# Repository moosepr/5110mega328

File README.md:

# 5110mega328
A tiny board with 5110 screen, atmega 328 and accelerometer

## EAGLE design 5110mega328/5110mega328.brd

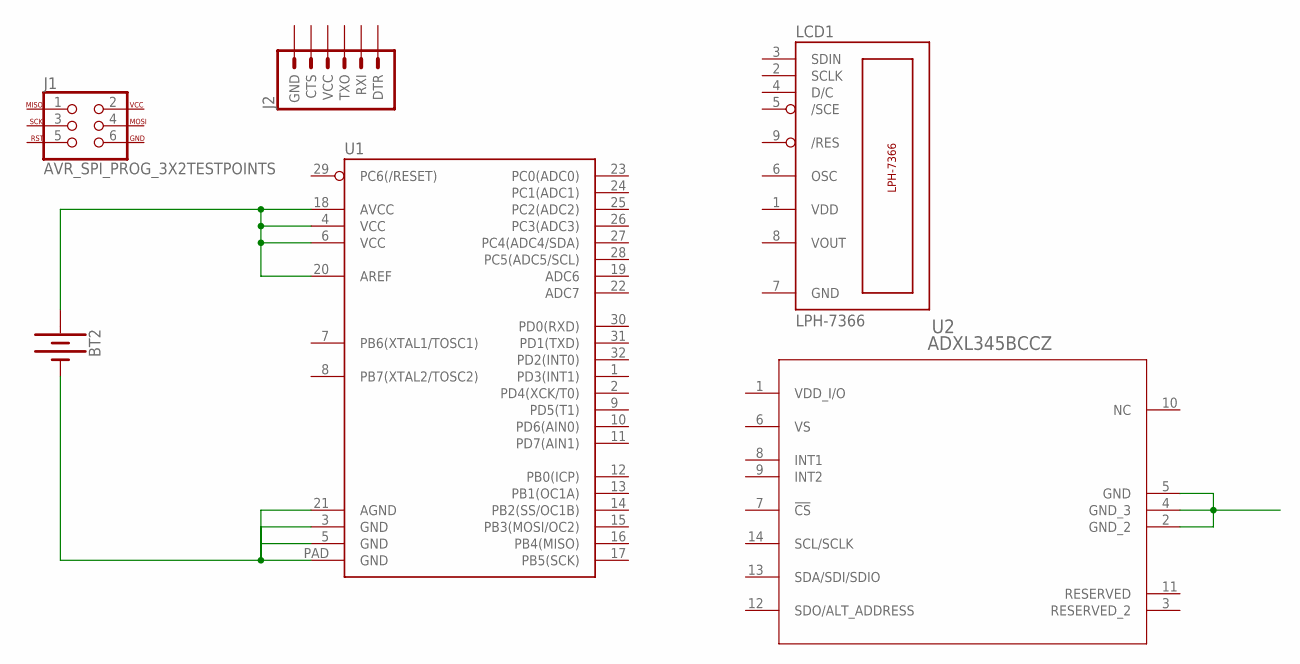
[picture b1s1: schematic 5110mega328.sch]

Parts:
BT2: BATTERY-20MM_SMD_4LEGS_OVERPASTE; BATTCON_20MM_4LEGS_OVERPASTE
J1: AVR_SPI_PROG_3X2TESTPOINTS; 2X3_TEST_POINTS
J2: 6_PIN_SERIAL_TARGETRA_SMT; 6_PIN_SERIAL_TARGET_SIDE_RA_SMT
LCD1: LPH-7366
U1: ATMEGA328P_MLFMLF32; MLF32-PAD
U2: ADXL345BCCZ; LGA_CC-14-1

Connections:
3V: BT2.1 (+), U1.4 (VCC), U1.6 (VCC), U1.18 (AVCC), U1.20 (AREF)
GND: BT2.2 (-), LCD1.7 (GND), U1.3 (GND), U1.5 (GND), U1.21 (AGND), U1.PAD (GND), U2.2 (GND_2), U2.4 (GND_3), U2.5 (GND)
VDD: LCD1.1 (VDD)

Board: 2 copper layers, 6 parts (4 on the bottom side), 2 nets, no tracks yet.

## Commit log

2017-12-29 just a base eagle setup

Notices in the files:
parts and their libraries:
SparkFun-Batteries: Licensing: Creative Commons ShareAlike 4.0 International - https://creativecommons.org/licenses/by-sa/4.0
